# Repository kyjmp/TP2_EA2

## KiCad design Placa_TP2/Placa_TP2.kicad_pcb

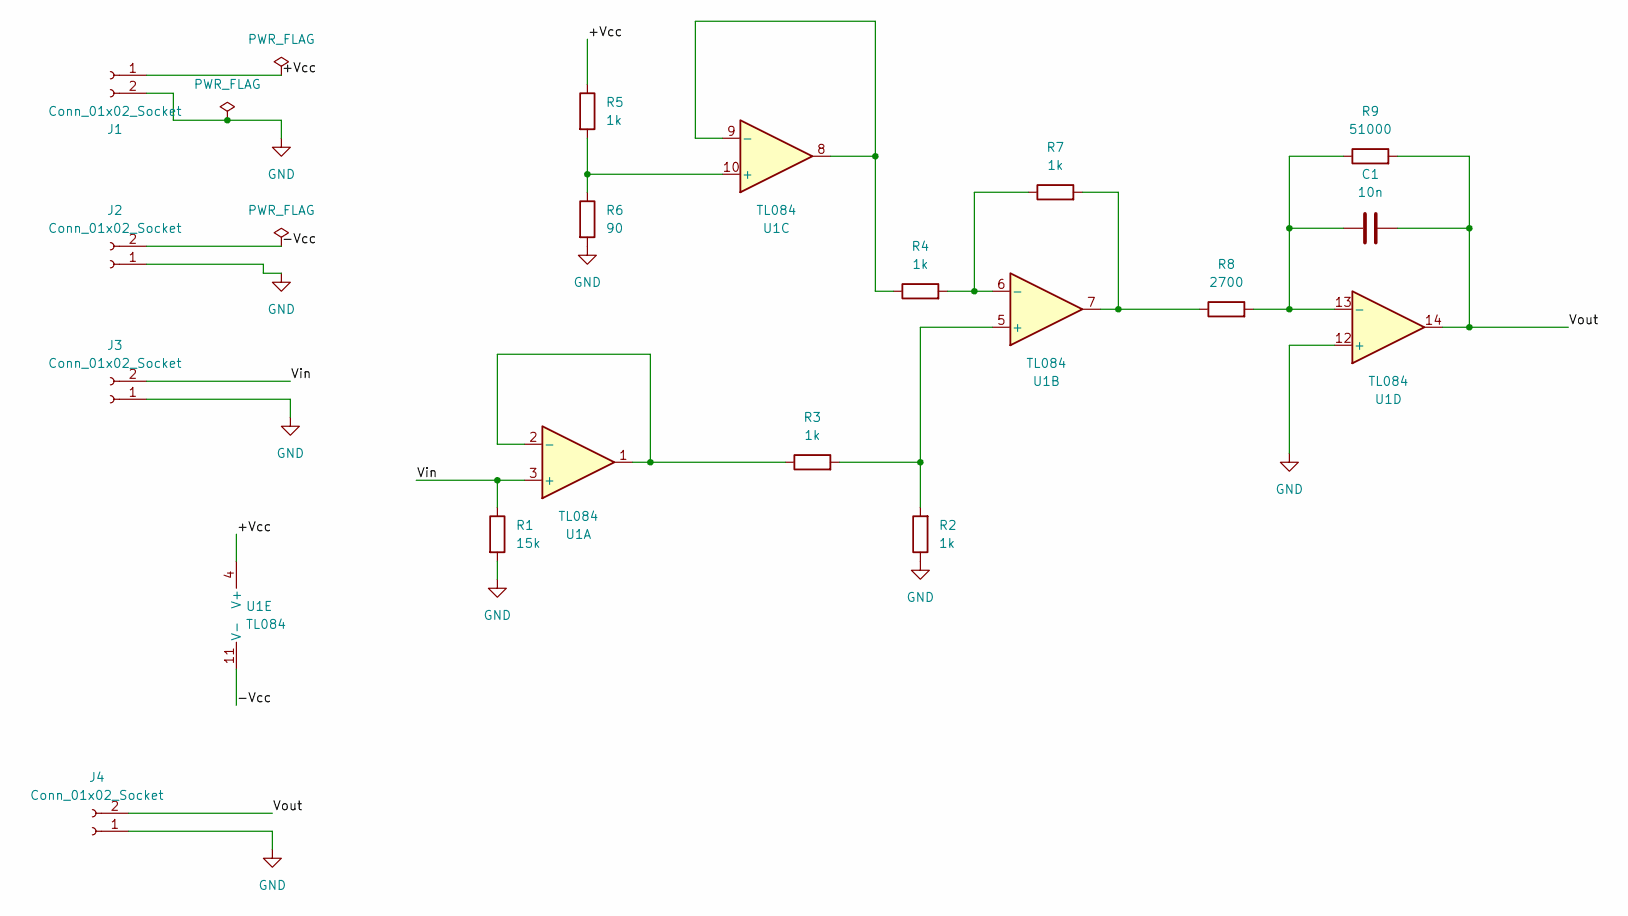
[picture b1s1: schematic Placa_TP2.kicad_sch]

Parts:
C1: 10n; CP_Radial_D6.3mm_P2.50mm
J1, J2, J3, J4: Conn_01x02_Socket; SolderWire-0.1sqmm_1x02_P3.6mm_D0.4mm_OD1mm
R1: 15k; R_Axial_DIN0204_L3.6mm_D1.6mm_P7.62mm_Horizontal
R2, R3, R4, R5, R7: 1k; R_Axial_DIN0204_L3.6mm_D1.6mm_P7.62mm_Horizontal
R6: 90; R_Axial_DIN0204_L3.6mm_D1.6mm_P7.62mm_Horizontal
R8: 2700; R_Axial_DIN0204_L3.6mm_D1.6mm_P7.62mm_Horizontal
R9: 51000; R_Axial_DIN0204_L3.6mm_D1.6mm_P7.62mm_Horizontal
U1: TL084; DIP-14_W7.62mm_Socket

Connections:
/+Vcc: J1.1, R5.1, U1.4 (V+)
/-Vcc: J2.2, U1.11 (V-)
/Vin: J3.2, R1.1, U1.3 (+)
/Vout: C1.2, J4.2, R9.2, U1.14
GND: J1.2, J2.1, J3.1, J4.1, R1.2, R2.1, R6.2, U1.12 (+)
unnamed: R7.2, R8.1, U1.7
unnamed: R3.1, U1.1, U1.2 (-)
unnamed: R2.2, R3.2, U1.5 (+)
unnamed: R4.2, R7.1, U1.6 (-)
unnamed: R5.2, R6.1, U1.10 (+)
unnamed: R4.1, U1.8, U1.9 (-)
unnamed: C1.1, R8.2, R9.1, U1.13 (-)

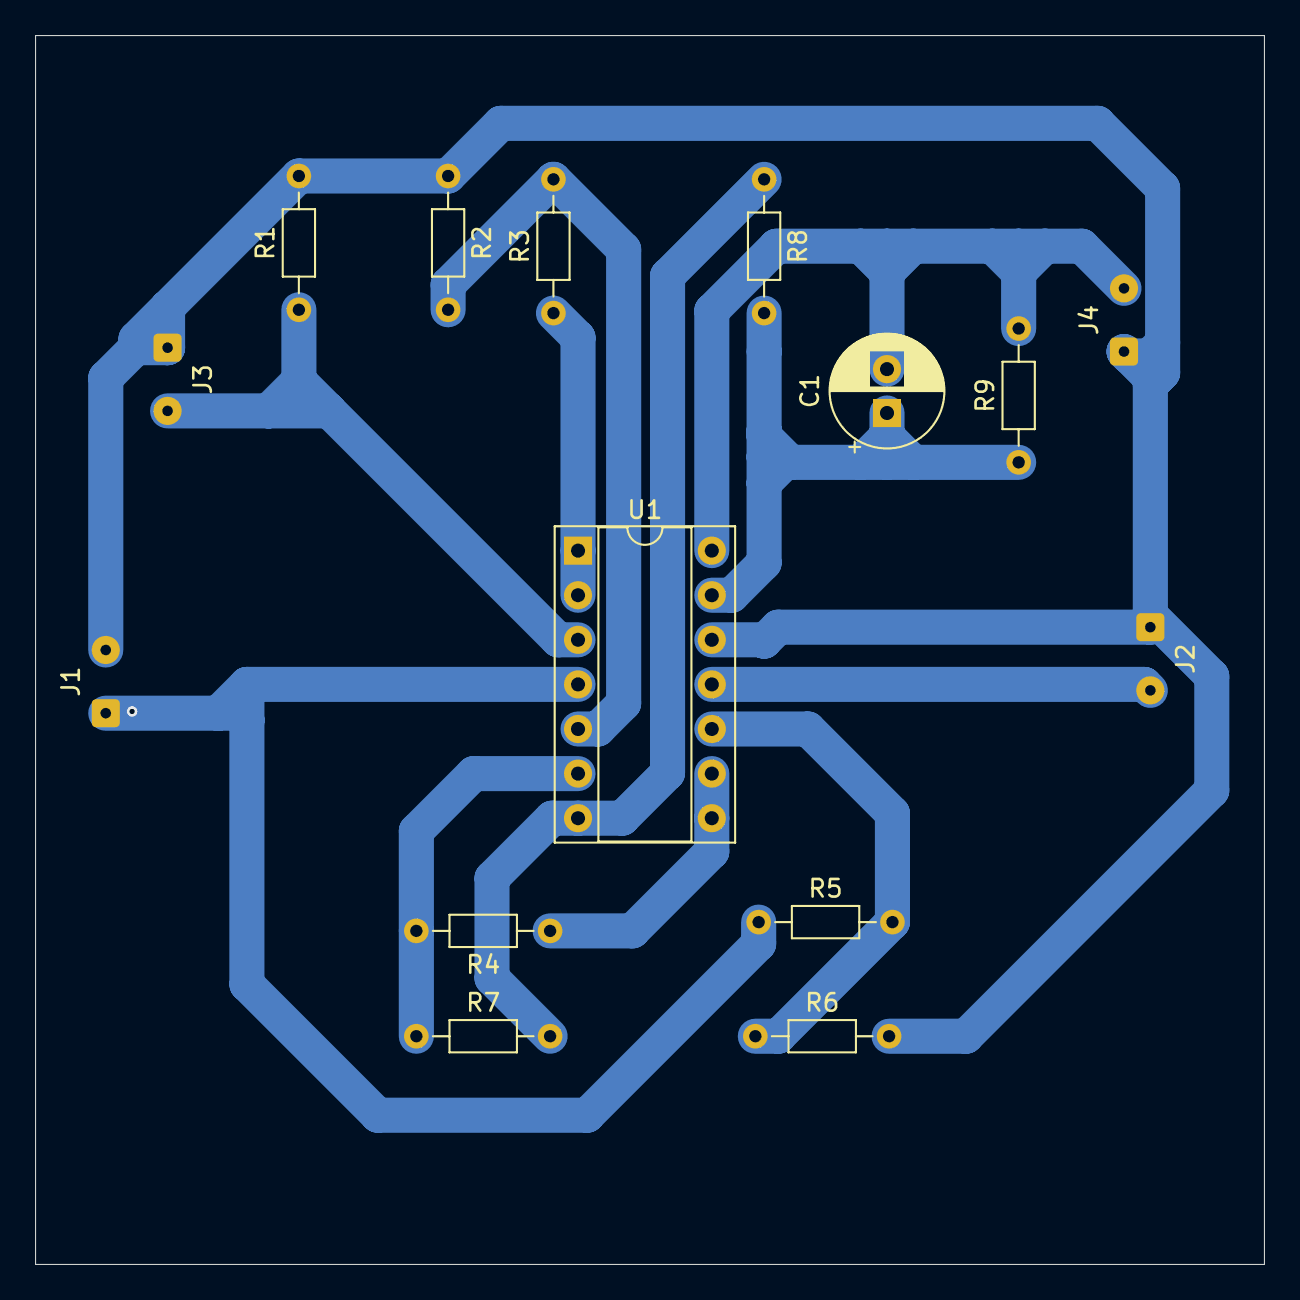
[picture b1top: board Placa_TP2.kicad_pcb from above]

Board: 2 copper layers, 70.0 x 70.0 mm, 15 parts (0 on the bottom side), 12 nets.

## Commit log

2025-05-12 primer commit
2025-05-12 carpeta de kicad
2025-05-12 Diseño esquematico
2025-05-12 mañana termino
2025-05-12 placa final
